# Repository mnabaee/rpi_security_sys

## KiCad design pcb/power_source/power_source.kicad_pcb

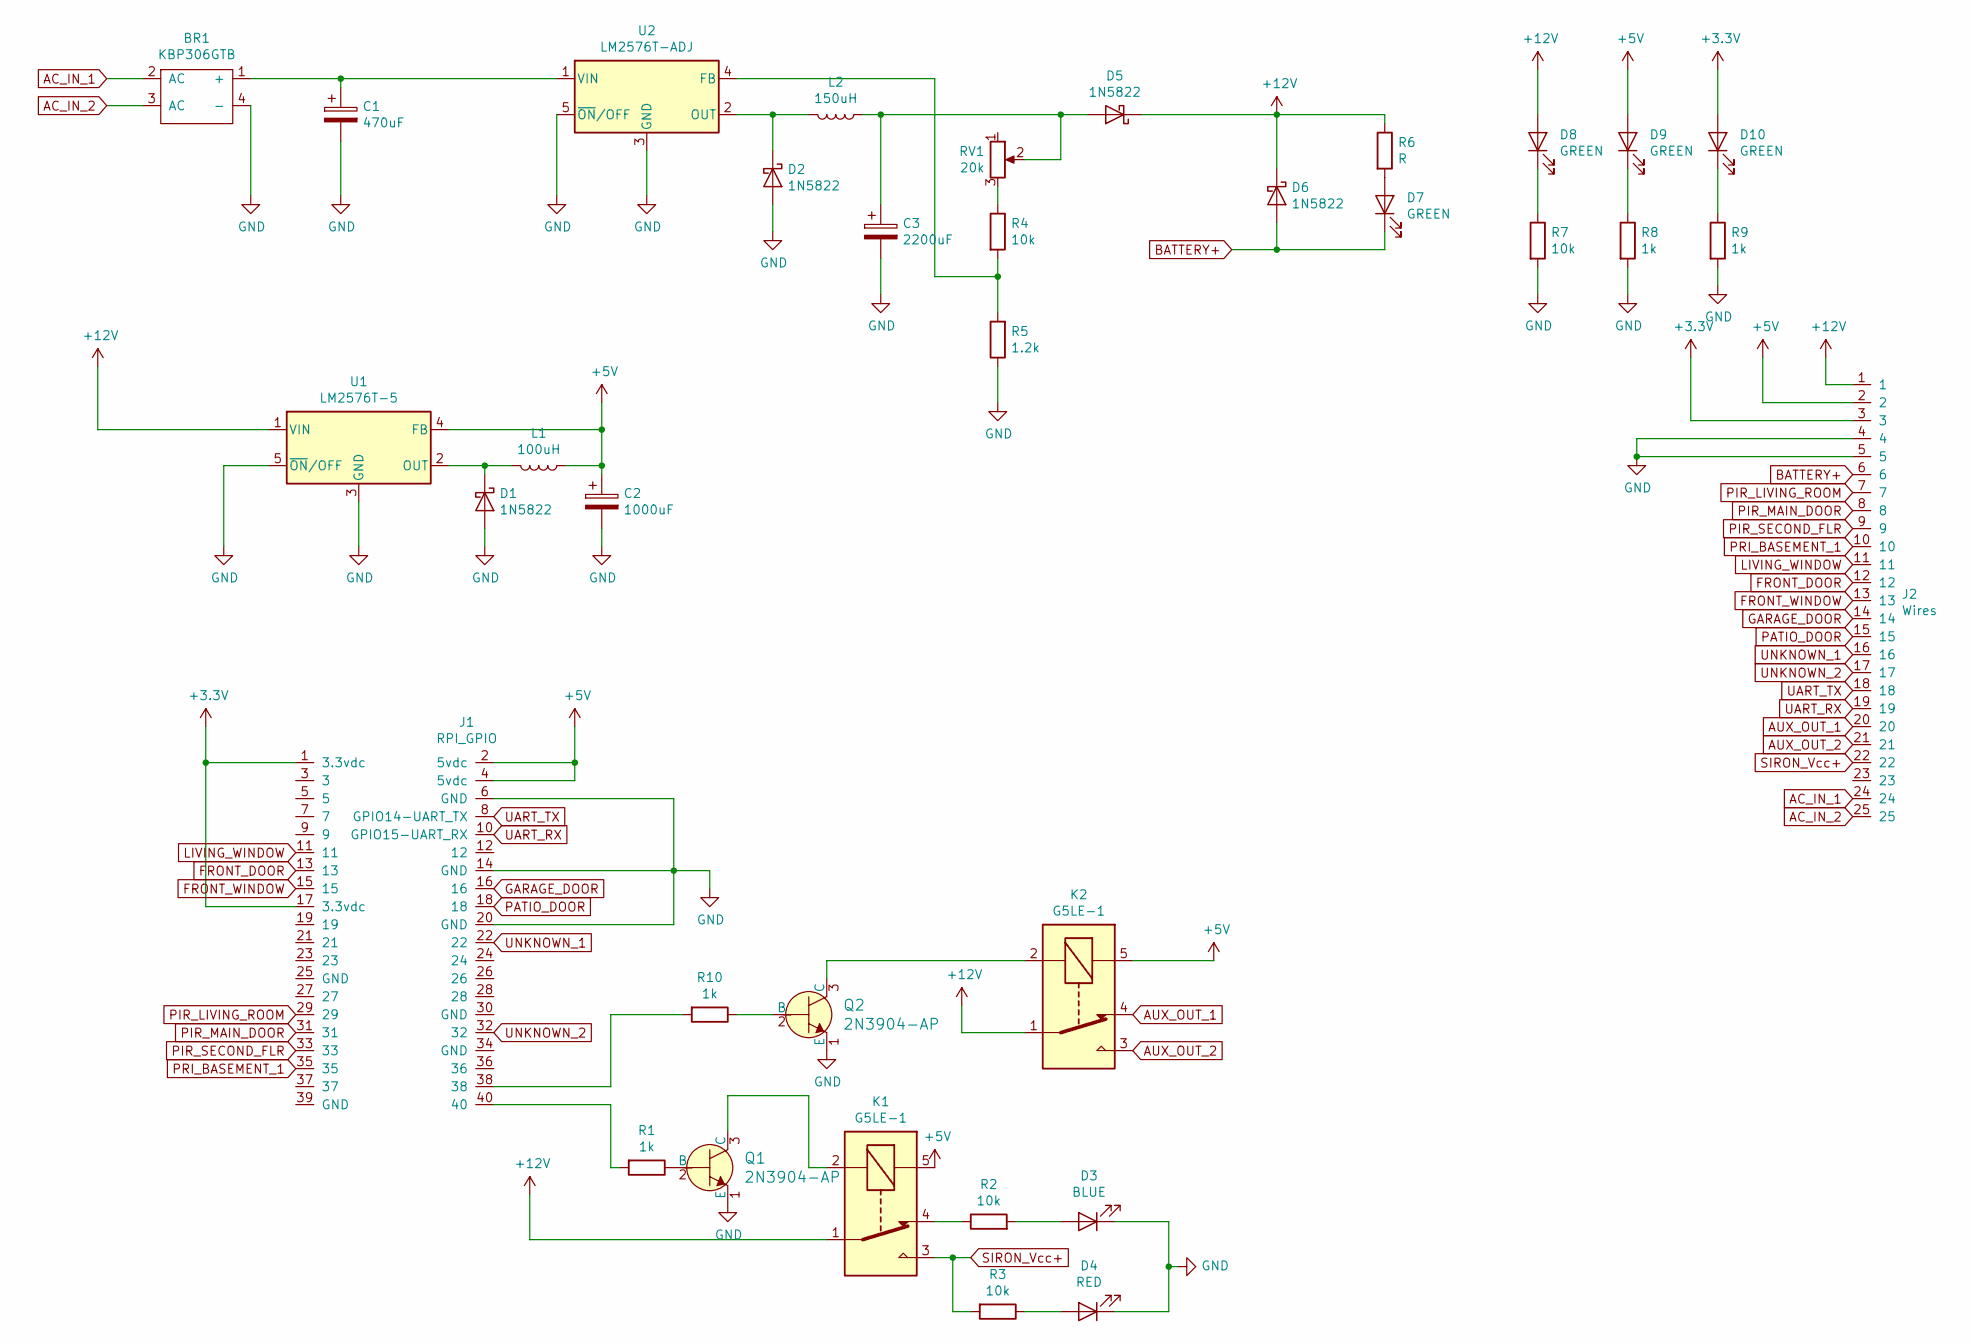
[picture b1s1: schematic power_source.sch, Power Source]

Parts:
BR1: KBP306GTB; KBP306GTB_BRIDGE_RECTIFIER_FTPT
C1: 470uF; CP_Radial_Tantal_D10.5mm_P5.00mm
C2: 1000uF; CP_Radial_Tantal_D10.5mm_P5.00mm
C3: 2200uF; CP_Radial_Tantal_D10.5mm_P5.00mm
D1, D2, D5, D6: 1N5822; D_DO-201AD_P12.70mm_Horizontal
D3: BLUE; LED_D5.0mm_Clear
D4: RED; LED_D5.0mm_Clear
D7, D8, D9, D10: GREEN; LED_D5.0mm_Clear
J1: RPI_GPIO; PinHeader_2x20_P2.54mm_Horizontal
J2: Wires; 2-282836-6_25_PIN_BLOCK_TERM
K1, K2: G5LE-1; Relay_SPDT_Omron-G5LE-1
L1: 100uH; L_Axial_L23.4mm_D12.7mm_P32.00mm_Horizontal_Vishay_IHA-203
L2: 150uH; L_Toroid_Vertical_L33.0mm_W17.8mm_P12.70mm_Pulse_KM-5
Q1, Q2: 2N3904-AP; 2n3903; MPN 2N3904-AP; Digi-Key_PN 2N3904-APCT-ND
R1, R8, R9, R10: 1k; R_Axial_DIN0204_L3.6mm_D1.6mm_P7.62mm_Horizontal
R2, R3, R4, R7: 10k; R_Axial_DIN0204_L3.6mm_D1.6mm_P7.62mm_Horizontal
R5: 1.2k; R_Axial_DIN0204_L3.6mm_D1.6mm_P7.62mm_Horizontal
R6: R; R_Axial_DIN0204_L3.6mm_D1.6mm_P7.62mm_Horizontal
RV1: 20k; Potentiometer_Piher_PT-10-V10_Vertical
U1: LM2576T-5; TO-220-5_Vertical
U2: LM2576T-ADJ; TO-220-5_Vertical

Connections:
+3V3: D10.2 (A), J1.1 (3.3vdc), J1.17 (3.3vdc), J2.3
+5V: C2.1, D9.2 (A), J1.2 (5vdc), J1.4 (5vdc), J2.2, K1.5, K2.5, L1.1, U1.4 (FB)
+12V: D5.1 (K), D6.1 (K), D8.2 (A), J2.1, K1.1, K2.1, R6.1, U1.1 (VIN)
AC_IN_1: BR1.2 (AC), J2.24
AC_IN_2: BR1.3 (AC), J2.25
AUX_OUT_1: J2.20, K2.4
AUX_OUT_2: J2.21, K2.3
BATTERY+: D6.2 (A), D7.1 (K), J2.6
FRONT_DOOR: J1.13, J2.12
FRONT_WINDOW: J1.15, J2.13
GARAGE_DOOR: J1.16, J2.14
GND: BR1.4 (-), C1.2, C2.2, C3.2, D1.2 (A), D2.2 (A), D3.1 (K), D4.1 (K), J1.6 (GND), J1.14 (GND), J1.20 (GND), J2.4, J2.5, Q1.1 (E), Q2.1 (E), R5.1, R7.2, R8.2, R9.2, U1.3 (GND), U1.5 (~ON~/OFF), U2.3 (GND), U2.5 (~ON~/OFF)
LIVING_WINDOW: J1.11, J2.11
unnamed: BR1.1 (+), C1.1, U2.1 (VIN)
unnamed: C3.1, D5.2 (A), L2.1, RV1.2
unnamed: D1.1 (K), L1.2, U1.2 (OUT)
unnamed: D2.1 (K), L2.2, U2.2 (OUT)
unnamed: D3.2 (A), R2.2
unnamed: D4.2 (A), R3.1
unnamed: D7.2 (A), R6.2
unnamed: D8.1 (K), R7.1
unnamed: D9.1 (K), R8.1
unnamed: D10.1 (K), R9.1
unnamed: J1.38, R10.2
unnamed: J1.40, R1.2
unnamed: K1.2, Q1.3 (C)
unnamed: K1.4, R2.1
unnamed: K2.2, Q2.3 (C)
unnamed: Q1.2 (B), R1.1
unnamed: Q2.2 (B), R10.1
unnamed: R4.1, RV1.3
unnamed: R4.2, R5.2, U2.4 (FB)
PATIO_DOOR: J1.18, J2.15
PIR_LIVING_ROOM: J1.29, J2.7
PIR_MAIN_DOOR: J1.31, J2.8
PIR_SECOND_FLR: J1.33, J2.9
PRI_BASEMENT_1: J1.35, J2.10
SIRON_Vcc+: J2.22, K1.3, R3.2
UART_RX: J1.10 (GPIO15-UART_RX), J2.19
UART_TX: J1.8 (GPIO14-UART_TX), J2.18
UNKNOWN_1: J1.22, J2.16
UNKNOWN_2: J1.32, J2.17

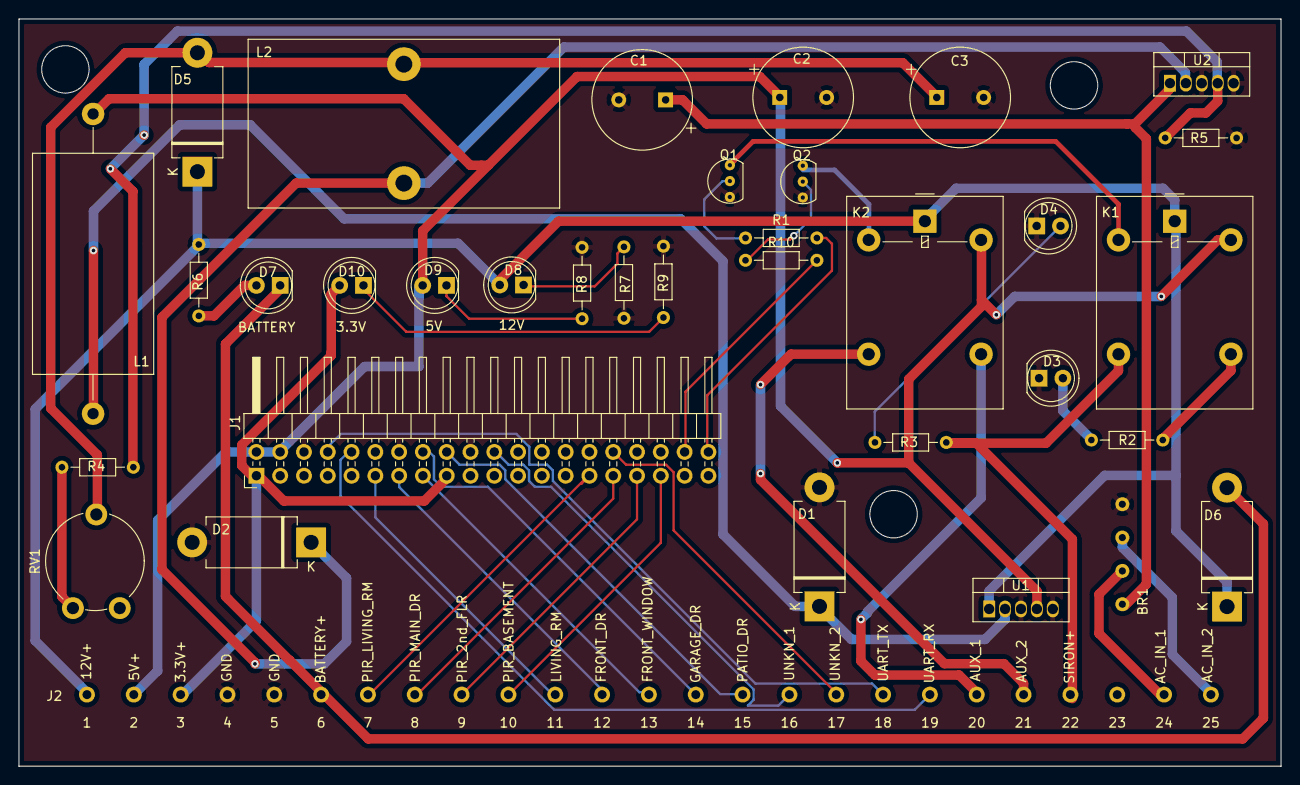
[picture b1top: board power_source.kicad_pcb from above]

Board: 2 copper layers, 134.7 x 79.8 mm, 35 parts (0 on the bottom side), 42 nets.

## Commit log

2019-12-10 adding pcb project
